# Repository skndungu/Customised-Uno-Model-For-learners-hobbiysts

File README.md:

# Customised-Uno-Model-For-learners-hobbiysts
This repo includes all the the files used in this design, and all the gerbers needed for its production

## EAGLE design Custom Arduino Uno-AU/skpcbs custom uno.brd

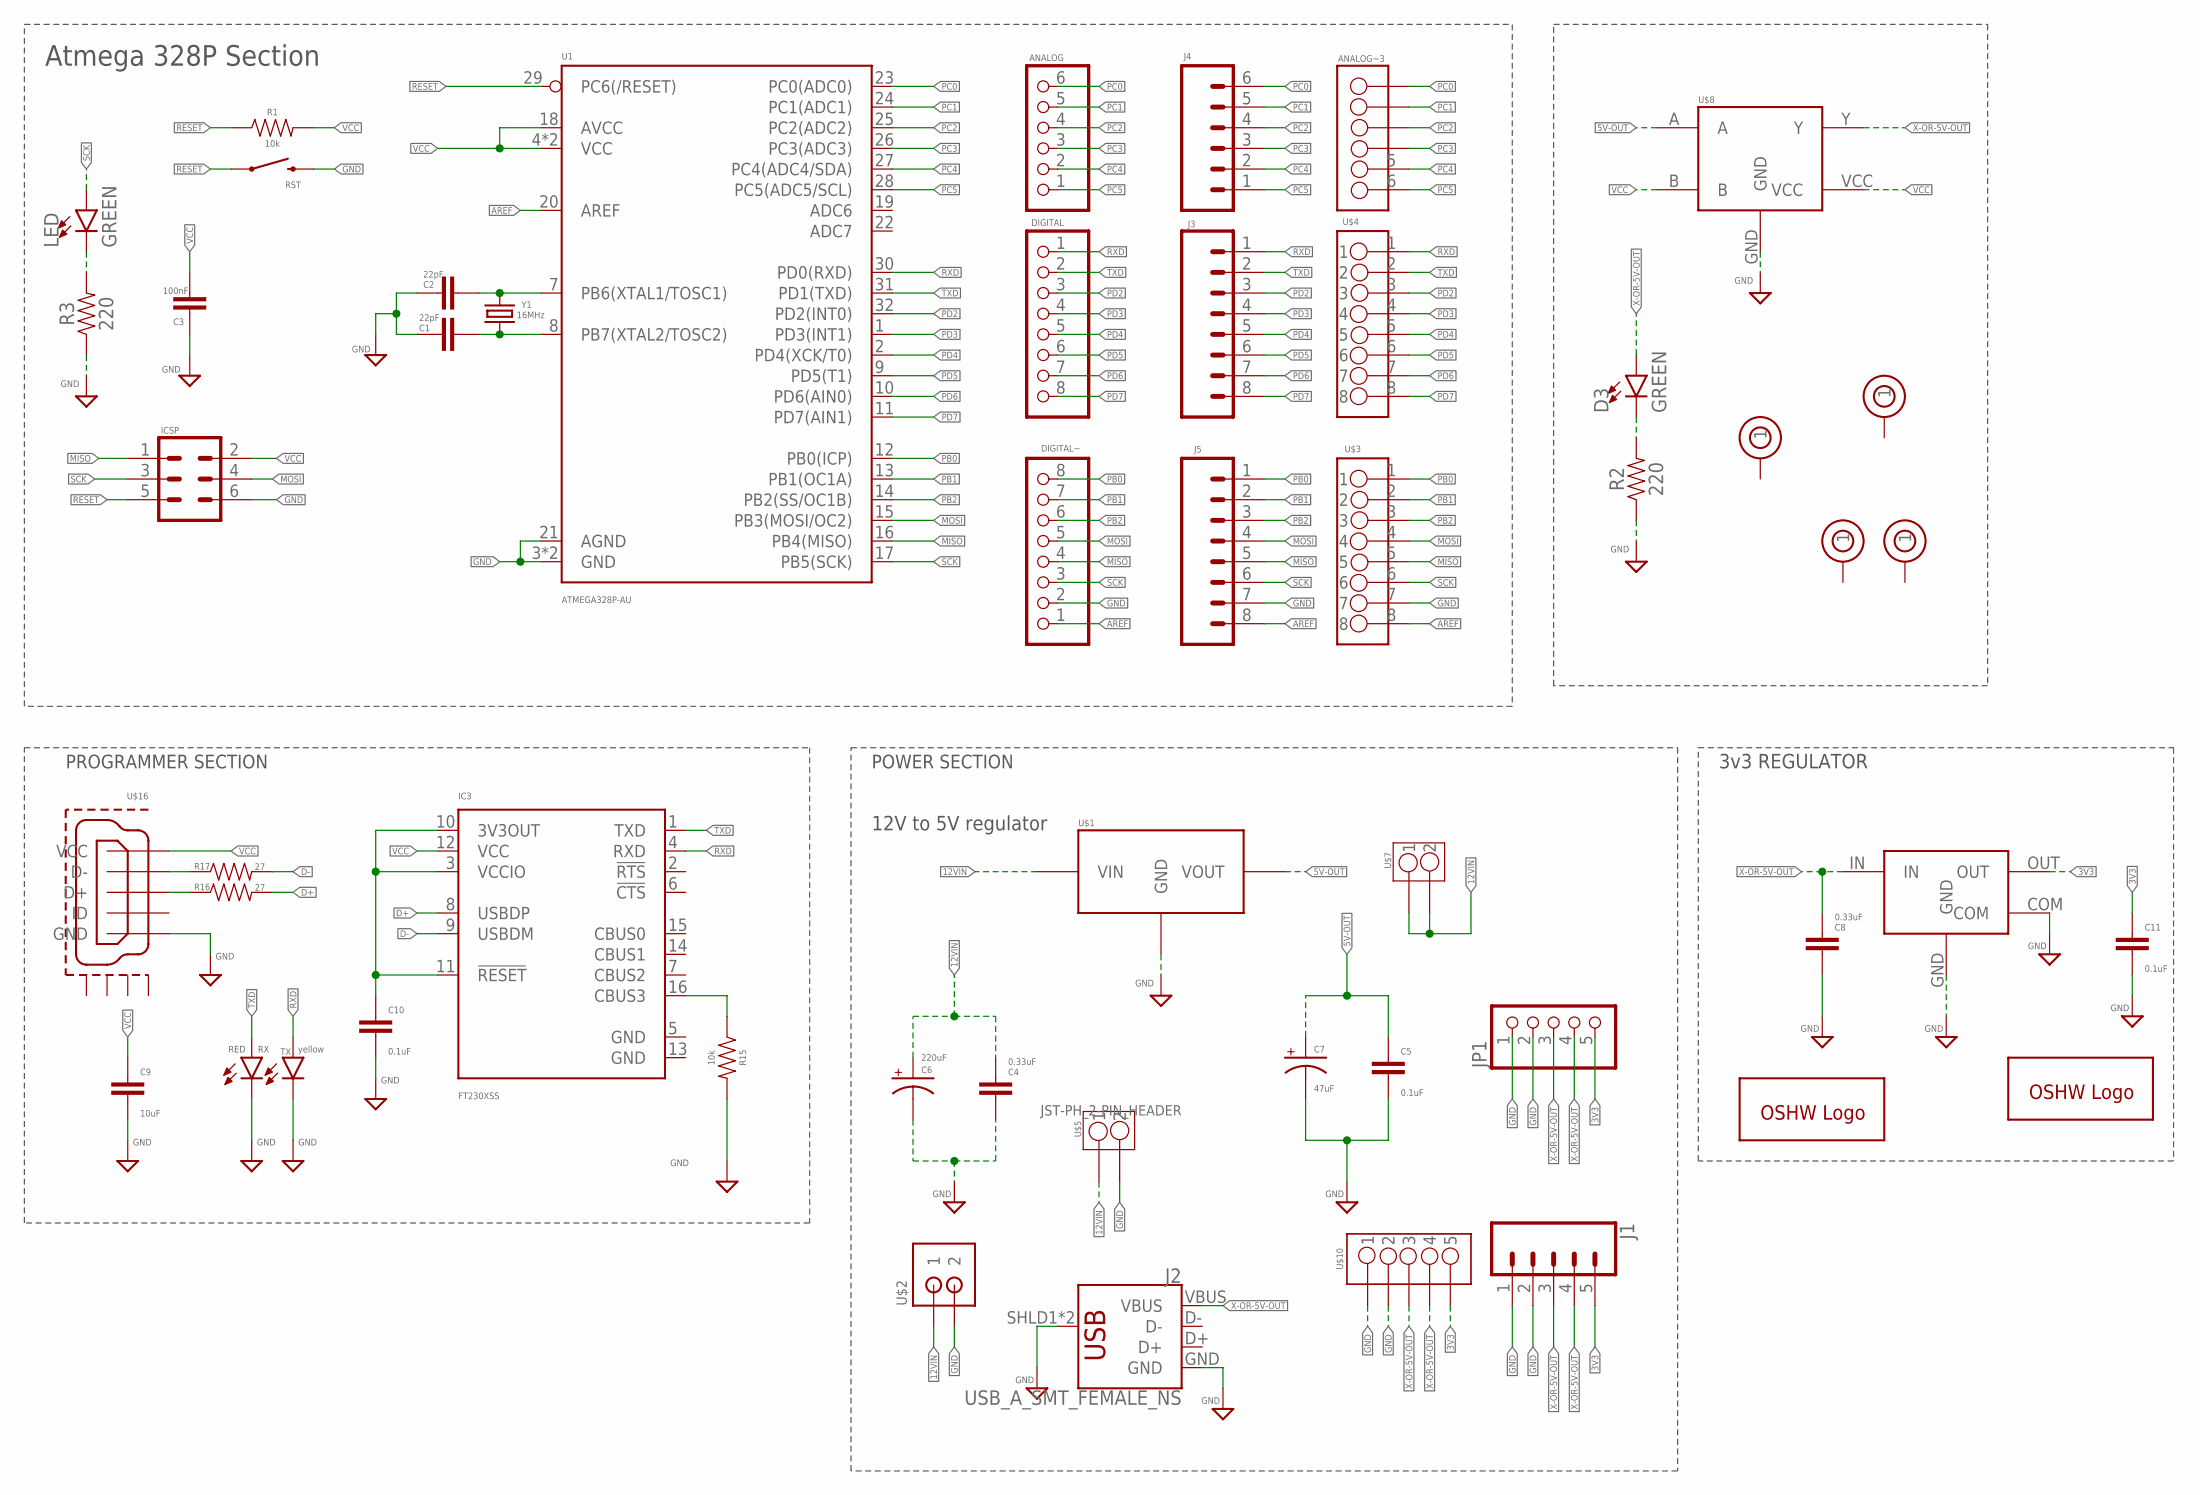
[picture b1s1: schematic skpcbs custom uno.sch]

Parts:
ANALOG: PINHD-1X6; 1X06
ANALOG~3: TERMINAL-BLOCKS-2.54MM-6PINS; TERMINAL-BLOCK-2.54MM-6PINS
C1, C2: 22pF; 0603
C3: 100nF; 0603
C4, C8: 0.33uF; 0603
C5, C10, C11: 0.1uF; 0603
C6: 220uF; 153CLV-0605
C7: 47uF; 153CLV-0605
C9: 10uF; 0603
D3: GREEN; LED-0603
DIGITAL: PINHD-1X8; 1X08
DIGITAL~: PINHD-1X8; 1X08
GOLD_ORB_SM1, GOLD_ORB_SM2: OSHWLOGOLOGO8MM; OSHW_8MM
IC3: FT230XSS; SSOP16
ICSP: CONN_03X2SHROUD; 2X3-SHROUDED
J1: CONN_05NO_SILK; 1X05_NO_SILK
J2: USB_A_SMT_FEMALE_NS; USB-A-S-NOSILK-FEMALE
J3, J5: CONN_08NO_SILK_FEMALE_PTH; 1X08_NO_SILK
J4: CONN_06NO_SILK_FEMALE_PTH; 1X06_NO_SILK
JP1: PINHD-1X5; 1X05
LED: GREEN; LED-1206
R1, R15: 10k; 0603
R2, R3: 220; 0603
R16, R17: 27; 0603
RST: MOMENTARY-SWITCH-SPST-SMD-5.2MM; TACTILE_SWITCH_SMD_5.2MM
RX: RED; LED-1206
TX: yellow; LED-1206
U1: ATMEGA328P-AU; TQFP32-08
U$1: L78M05CDT-TR
U$2: JST-PH_2-PIN_HEADER; JST_B2B-PH_HEADER
U$3, U$4: TERMINAL-BLOCK-2.54MM-8PINS
U$5, U$7: TERMINAL-BLOCK-2.54MM-2PINS; TERMINAL-BLOCK-2.54MM-2PIN
U$6, U$11, U$12, U$13: 3MM-THROUGH-HOLE
U$8: NC7SZ86M5X
U$9: UA78M33CDCYR
U$10: TERMINAL-BLOCK-2.54MM-5PINS
U$16: MICRO-USB-RECEPTACLE47589-0001; 47589-0001
Y1: 16MHz; CRYSTAL-SMD-5X3.2-4PAD

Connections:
3V3: C11.1, J1.5, JP1.5, U$9.OUT, U$10.5
5V-OUT: C5.1, C7.+, U$1.VOUT, U$8.A
12VIN: C4.1, C6.+, U$1.VIN, U$2.P1 (1), U$5.1, U$7.1, U$7.2
AREF: DIGITAL~.1, J5.8, U1.20 (AREF), U$3.8
D+: IC3.8 (USBDP), R16.2
D-: IC3.9 (USBDM), R17.2
GND: C1.2, C2.1, C3.2, C4.2, C5.2, C6.-, C7.-, C8.2, C9.2, C10.2, C11.2, DIGITAL~.2, IC3.5 (GND), IC3.13 (GND), ICSP.6, J1.1, J1.2, J2.GND, J2.SHLD1 (SHIELD), J2.SHLD2 (SHIELD), J5.7, JP1.1, JP1.2, R2.1, R3.1, R15.2, RST.3 (2), RX.C, TX.C, U1.3 (GND), U1.5 (GND), U1.21 (AGND), U$1.GND, U$2.P2 (2), U$3.7, U$5.2, U$8.GND, U$9.COM, U$9.GND, U$10.1, U$10.2, U$16.GND
MISO: DIGITAL~.4, ICSP.1, J5.5, U1.16 (PB4(MISO)), U$3.5
MOSI: DIGITAL~.5, ICSP.4, J5.4, U1.15 (PB3(MOSI/OC2)), U$3.4
unnamed: C2.2, U1.7 (PB6(XTAL1/TOSC1)), Y1.3 (2)
unnamed: C1.1, U1.8 (PB7(XTAL2/TOSC2)), Y1.1
unnamed: LED.C, R3.2
unnamed: D3.C, R2.2
unnamed: IC3.16 (CBUS3), R15.1
unnamed: C10.1, IC3.3 (VCCIO), IC3.10 (3V3OUT), IC3.11 (!RESET)
unnamed: R16.1, U$16.D+
unnamed: R17.1, U$16.D-
PB0: DIGITAL~.8, J5.1, U1.12 (PB0(ICP)), U$3.1
PB1: DIGITAL~.7, J5.2, U1.13 (PB1(OC1A)), U$3.2
PB2: DIGITAL~.6, J5.3, U1.14 (PB2(SS/OC1B)), U$3.3
PC0: ANALOG.6, ANALOG~3.1, J4.6, U1.23 (PC0(ADC0))
PC1: ANALOG.5, ANALOG~3.2, J4.5, U1.24 (PC1(ADC1))
PC2: ANALOG.4, ANALOG~3.3, J4.4, U1.25 (PC2(ADC2))
PC3: ANALOG.3, ANALOG~3.4, J4.3, U1.26 (PC3(ADC3))
PC4: ANALOG.2, ANALOG~3.5, J4.2, U1.27 (PC4(ADC4/SDA))
PC5: ANALOG.1, ANALOG~3.6, J4.1, U1.28 (PC5(ADC5/SCL))
PD2: DIGITAL.3, J3.3, U1.32 (PD2(INT0)), U$4.3
PD3: DIGITAL.4, J3.4, U1.1 (PD3(INT1)), U$4.4
PD4: DIGITAL.5, J3.5, U1.2 (PD4(XCK/T0)), U$4.5
PD5: DIGITAL.6, J3.6, U1.9 (PD5(T1)), U$4.6
PD6: DIGITAL.7, J3.7, U1.10 (PD6(AIN0)), U$4.7
PD7: DIGITAL.8, J3.8, U1.11 (PD7(AIN1)), U$4.8
RESET: ICSP.5, R1.1, RST.1, U1.29 (PC6(/RESET))
RXD: DIGITAL.1, IC3.4 (RXD), J3.1, TX.A, U1.30 (PD0(RXD)), U$4.1
SCK: DIGITAL~.3, ICSP.3, J5.6, LED.A, U1.17 (PB5(SCK)), U$3.6
TXD: DIGITAL.2, IC3.1 (TXD), J3.2, RX.A, U1.31 (PD1(TXD)), U$4.2
VCC: C3.1, C9.1, IC3.12 (VCC), ICSP.2, R1.2, U1.4 (VCC), U1.6 (VCC), U1.18 (AVCC), U$8.B, U$8.VCC, U$16.V-BUS (VCC)
X-OR-5V-OUT: C8.1, D3.A, J1.3, J1.4, J2.VBUS, JP1.3, JP1.4, U$8.Y, U$9.IN, U$10.3, U$10.4

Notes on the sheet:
Atmega 328P Section
PROGRAMMER SECTION
POWER SECTION
12V to 5V regulator
3v3 REGULATOR

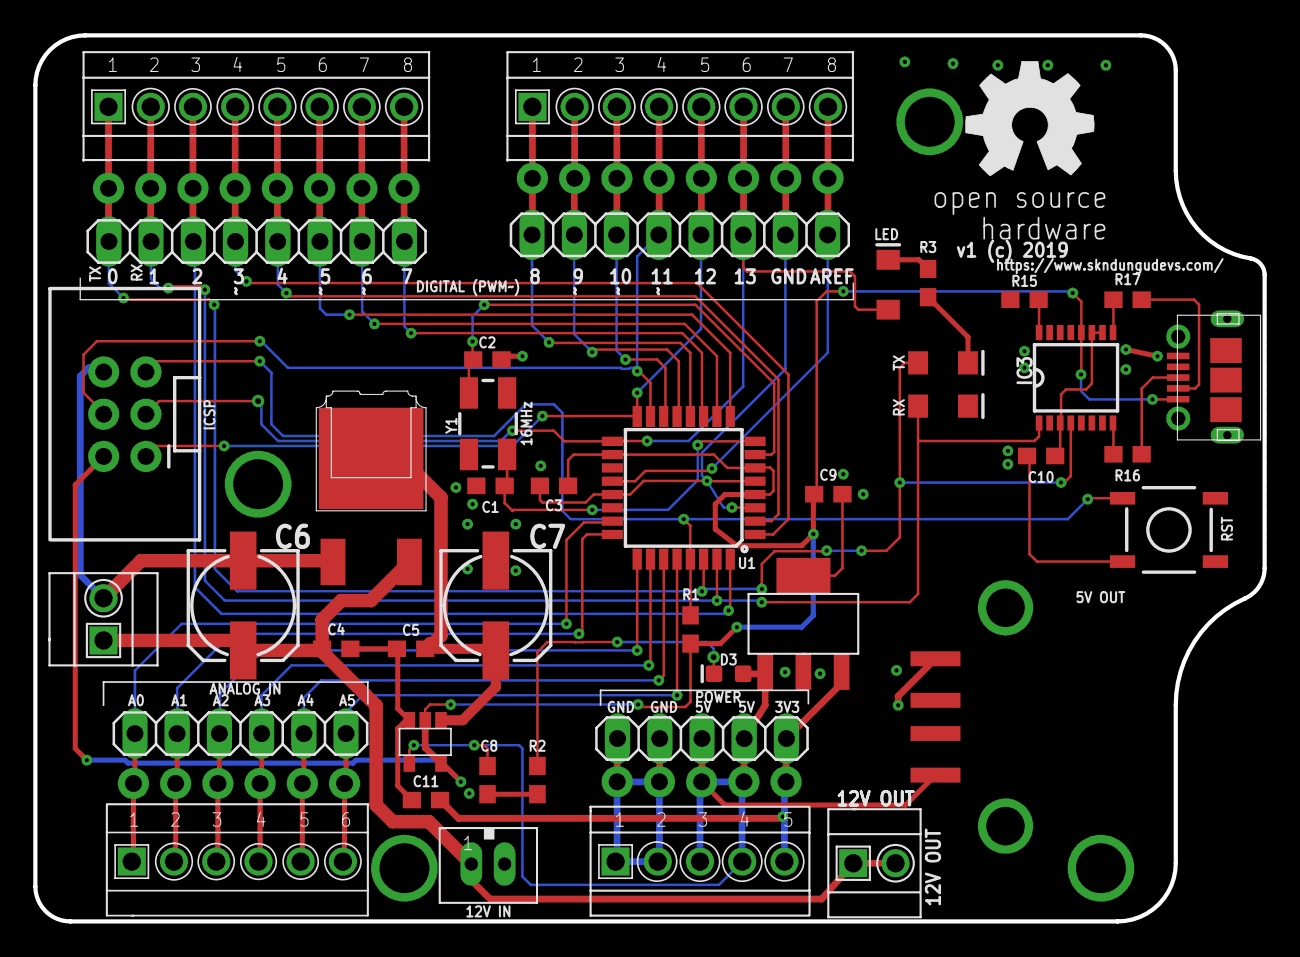
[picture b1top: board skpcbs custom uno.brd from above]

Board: 2 copper layers, 73.9 x 53.3 mm, 52 parts (1 on the bottom side), 38 nets.

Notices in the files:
Custom Arduino Uno-AU/skpcbs custom uno.brd:
v1 (c) 2019
parts and their libraries:
SparkFun-Capacitors: Licensing: Creative Commons ShareAlike 4.0 International - https://creativecommons.org/licenses/by-sa/4.0
con-molex-usb: (C) 2014 Tomasz Boleslaw CEDRO, cederom@tlen.pl, http://www.tomek.cedro.info.
